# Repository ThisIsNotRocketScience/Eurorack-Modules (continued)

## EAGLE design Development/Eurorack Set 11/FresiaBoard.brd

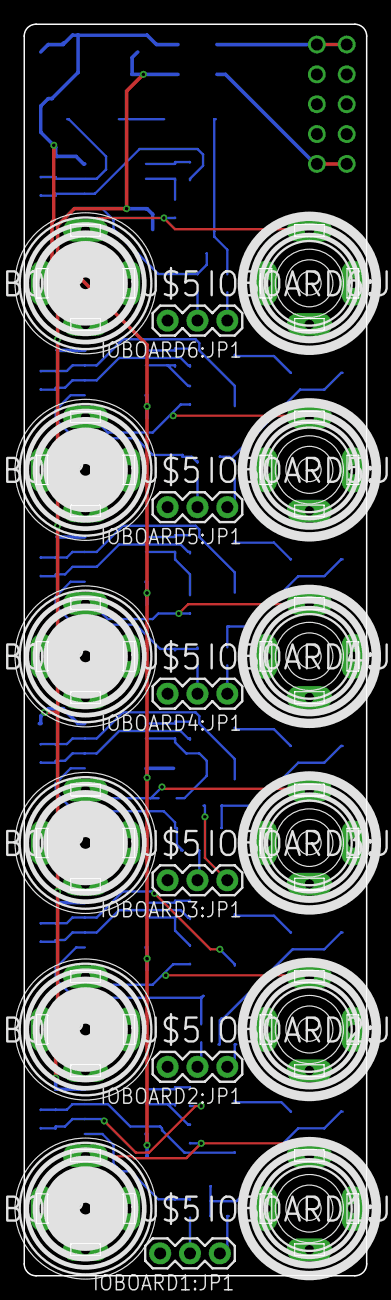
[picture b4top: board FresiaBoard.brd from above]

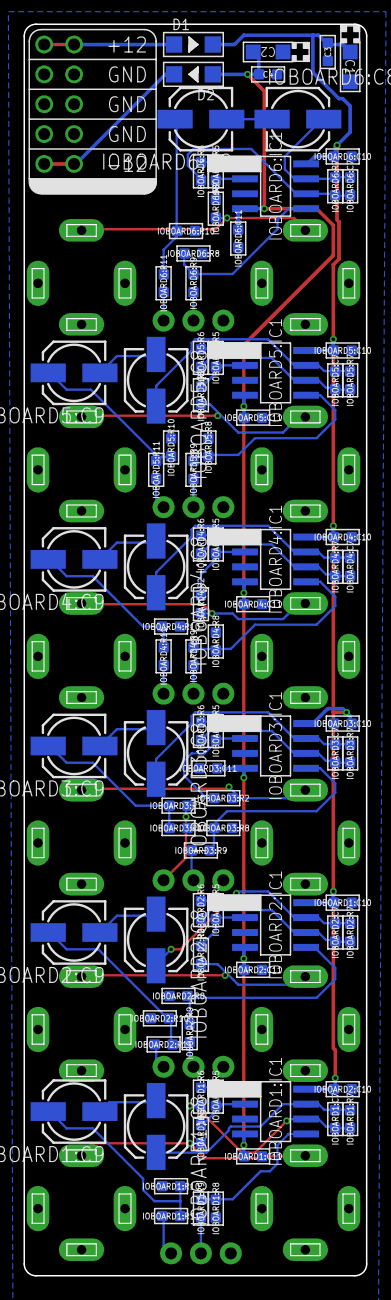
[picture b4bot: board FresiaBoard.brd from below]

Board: 2 copper layers, 29.1 x 106.5 mm, 110 parts (91 on the bottom side), 65 nets.

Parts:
C1, C2: 10uF; CASE-A_3216
C3, C4: 100nF; C0603
D1, D2: 1N4001; SOD123
IOBOARD1:C7, IOBOARD2:C7, IOBOARD3:C7, IOBOARD4:C7, IOBOARD5:C7, IOBOARD6:C7: 22p; C0603
IOBOARD1:C8, IOBOARD1:C9, IOBOARD2:C8, IOBOARD2:C9, IOBOARD3:C8, IOBOARD3:C9, IOBOARD4:C8, IOBOARD4:C9, IOBOARD5:C8, IOBOARD5:C9, IOBOARD6:C8, IOBOARD6:C9: 220uF; 153CLV-0505
IOBOARD1:C10, IOBOARD1:C11, IOBOARD2:C10, IOBOARD2:C11, IOBOARD3:C10, IOBOARD3:C11, IOBOARD4:C10, IOBOARD4:C11, IOBOARD5:C10, IOBOARD5:C11, IOBOARD6:C10, IOBOARD6:C11: 100nF; C0603
IOBOARD1:IC1, IOBOARD2:IC1, IOBOARD3:IC1, IOBOARD4:IC1, IOBOARD5:IC1, IOBOARD6:IC1: NE5532D; SO08
IOBOARD1:J1, IOBOARD2:J1, IOBOARD3:J1, IOBOARD4:J1, IOBOARD5:J1, IOBOARD6:J1: PJ-341; 3.5MM-JACK-SWITCH-13MM-OUTPUT
IOBOARD1:JP1, IOBOARD2:JP1, IOBOARD3:JP1, IOBOARD4:JP1, IOBOARD5:JP1, IOBOARD6:JP1: 1X03
IOBOARD1:R2, IOBOARD2:R2, IOBOARD3:R2, IOBOARD4:R2, IOBOARD5:R2, IOBOARD6:R2: 100k; R0603
IOBOARD1:R5, IOBOARD2:R5, IOBOARD3:R5, IOBOARD4:R5, IOBOARD5:R5, IOBOARD6:R5: 220k; R0603
IOBOARD1:R6, IOBOARD1:R7, IOBOARD2:R6, IOBOARD2:R7, IOBOARD3:R6, IOBOARD3:R7, IOBOARD4:R6, IOBOARD4:R7, IOBOARD5:R6, IOBOARD5:R7, IOBOARD6:R6, IOBOARD6:R7: 4.7k; R0603
IOBOARD1:R8, IOBOARD1:R9, IOBOARD2:R8, IOBOARD2:R9, IOBOARD3:R8, IOBOARD3:R9, IOBOARD4:R8, IOBOARD4:R9, IOBOARD5:R8, IOBOARD5:R9, IOBOARD6:R8, IOBOARD6:R9: 27; R0603
IOBOARD1:R10, IOBOARD2:R10, IOBOARD3:R10, IOBOARD4:R10, IOBOARD5:R10, IOBOARD6:R10: 22k; R0603
IOBOARD1:R11, IOBOARD2:R11, IOBOARD3:R11, IOBOARD4:R11, IOBOARD5:R11, IOBOARD6:R11: 56; R0603
IOBOARD1:U$5, IOBOARD2:U$5, IOBOARD3:U$5, IOBOARD4:U$5, IOBOARD5:U$5, IOBOARD6:U$5: PJ-341; 3.5MM-JACK-SWITCH-13MM-INPUT
PCB1: EURORACK_PCB6HP; EURORACK6HPPCB
U$1: POWER_SIMPLE10; POWER_10

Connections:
12V: C1.+, C3.2, D1.-, IOBOARD1:C10.1, IOBOARD1:IC1.8, IOBOARD2:C10.1, IOBOARD2:IC1.8, IOBOARD3:C10.1, IOBOARD3:IC1.8, IOBOARD4:C10.1, IOBOARD4:IC1.8, IOBOARD5:C10.1, IOBOARD5:IC1.8, IOBOARD6:C10.1, IOBOARD6:IC1.8
-12V: C2.-, C4.1, D2.+, IOBOARD1:C11.1, IOBOARD1:IC1.4, IOBOARD2:C11.1, IOBOARD2:IC1.4, IOBOARD3:C11.1, IOBOARD3:IC1.4, IOBOARD4:C11.1, IOBOARD4:IC1.4, IOBOARD5:C11.1, IOBOARD5:IC1.4, IOBOARD6:C11.1, IOBOARD6:IC1.4
GND: C1.-, C2.+, C3.1, C4.2, IOBOARD1:C10.2, IOBOARD1:C11.2, IOBOARD1:IC1.3, IOBOARD1:J1.RING@3, IOBOARD1:JP1.3, IOBOARD1:R8.2, IOBOARD1:R10.1, IOBOARD1:U$5.RING@3, IOBOARD1:U$5.SWITCH@3, IOBOARD2:C10.2, IOBOARD2:C11.2, IOBOARD2:IC1.3, IOBOARD2:J1.RING@3, IOBOARD2:JP1.3, IOBOARD2:R8.2, IOBOARD2:R10.1, IOBOARD2:U$5.RING@3, IOBOARD2:U$5.SWITCH@3, IOBOARD3:C10.2, IOBOARD3:C11.2, IOBOARD3:IC1.3, IOBOARD3:J1.RING@3, IOBOARD3:JP1.3, IOBOARD3:R8.2, IOBOARD3:R10.1, IOBOARD3:U$5.RING@3, IOBOARD3:U$5.SWITCH@3, IOBOARD4:C10.2, IOBOARD4:C11.2, IOBOARD4:IC1.3, IOBOARD4:J1.RING@3, IOBOARD4:JP1.3, IOBOARD4:R8.2, IOBOARD4:R10.1, IOBOARD4:U$5.RING@3, IOBOARD4:U$5.SWITCH@3, IOBOARD5:C10.2, IOBOARD5:C11.2, IOBOARD5:IC1.3, IOBOARD5:J1.RING@3, IOBOARD5:JP1.3, IOBOARD5:R8.2, IOBOARD5:R10.1, IOBOARD5:U$5.RING@3, IOBOARD5:U$5.SWITCH@3, IOBOARD6:C10.2, IOBOARD6:C11.2, IOBOARD6:IC1.3, IOBOARD6:J1.RING@3, IOBOARD6:JP1.3, IOBOARD6:R8.2, IOBOARD6:R10.1, IOBOARD6:U$5.RING@3, IOBOARD6:U$5.SWITCH@3, U$1.3, U$1.4, U$1.5, U$1.6, U$1.7, U$1.8
IOBOARD1:N$2: IOBOARD1:C7.1, IOBOARD1:C8.+, IOBOARD1:IC1.7, IOBOARD1:R7.1
IOBOARD1:N$3: IOBOARD1:IC1.5, IOBOARD1:R8.1, IOBOARD1:R9.1
IOBOARD1:N$4: IOBOARD1:C7.2, IOBOARD1:IC1.6, IOBOARD1:R6.1, IOBOARD1:R7.2
IOBOARD1:N$5: IOBOARD1:IC1.2, IOBOARD1:R2.2, IOBOARD1:R5.2
IOBOARD1:N$6: IOBOARD1:IC1.1, IOBOARD1:R5.1, IOBOARD1:R6.2
IOBOARD1:N$7: IOBOARD1:J1.TIP@3, IOBOARD1:R2.1, IOBOARD1:U$5.TIP@3
IOBOARD1:N$8: IOBOARD1:C8.-, IOBOARD1:C9.-
IOBOARD1:N$9: IOBOARD1:C9.+, IOBOARD1:R10.2, IOBOARD1:R11.2
IOBOARD1:RIGHT_MID: IOBOARD1:JP1.2, IOBOARD1:R9.2
IOBOARD1:RIGHT_TIP: IOBOARD1:JP1.1, IOBOARD1:R11.1
IOBOARD2:N$2: IOBOARD2:C7.1, IOBOARD2:C8.+, IOBOARD2:IC1.7, IOBOARD2:R7.1
IOBOARD2:N$3: IOBOARD2:IC1.5, IOBOARD2:R8.1, IOBOARD2:R9.1
IOBOARD2:N$4: IOBOARD2:C7.2, IOBOARD2:IC1.6, IOBOARD2:R6.1, IOBOARD2:R7.2
IOBOARD2:N$5: IOBOARD2:IC1.2, IOBOARD2:R2.2, IOBOARD2:R5.2
IOBOARD2:N$6: IOBOARD2:IC1.1, IOBOARD2:R5.1, IOBOARD2:R6.2
IOBOARD2:N$7: IOBOARD2:J1.TIP@3, IOBOARD2:R2.1, IOBOARD2:U$5.TIP@3
IOBOARD2:N$8: IOBOARD2:C8.-, IOBOARD2:C9.-
IOBOARD2:N$9: IOBOARD2:C9.+, IOBOARD2:R10.2, IOBOARD2:R11.2
IOBOARD2:RIGHT_MID: IOBOARD2:JP1.2, IOBOARD2:R9.2
IOBOARD2:RIGHT_TIP: IOBOARD2:JP1.1, IOBOARD2:R11.1
IOBOARD3:N$2: IOBOARD3:C7.1, IOBOARD3:C8.+, IOBOARD3:IC1.7, IOBOARD3:R7.1
IOBOARD3:N$3: IOBOARD3:IC1.5, IOBOARD3:R8.1, IOBOARD3:R9.1
IOBOARD3:N$4: IOBOARD3:C7.2, IOBOARD3:IC1.6, IOBOARD3:R6.1, IOBOARD3:R7.2
IOBOARD3:N$5: IOBOARD3:IC1.2, IOBOARD3:R2.2, IOBOARD3:R5.2
IOBOARD3:N$6: IOBOARD3:IC1.1, IOBOARD3:R5.1, IOBOARD3:R6.2
IOBOARD3:N$7: IOBOARD3:J1.TIP@3, IOBOARD3:R2.1, IOBOARD3:U$5.TIP@3
IOBOARD3:N$8: IOBOARD3:C8.-, IOBOARD3:C9.-
IOBOARD3:N$9: IOBOARD3:C9.+, IOBOARD3:R10.2, IOBOARD3:R11.2
IOBOARD3:RIGHT_MID: IOBOARD3:JP1.2, IOBOARD3:R9.2
IOBOARD3:RIGHT_TIP: IOBOARD3:JP1.1, IOBOARD3:R11.1
IOBOARD4:N$2: IOBOARD4:C7.1, IOBOARD4:C8.+, IOBOARD4:IC1.7, IOBOARD4:R7.1
IOBOARD4:N$3: IOBOARD4:IC1.5, IOBOARD4:R8.1, IOBOARD4:R9.1
IOBOARD4:N$4: IOBOARD4:C7.2, IOBOARD4:IC1.6, IOBOARD4:R6.1, IOBOARD4:R7.2
IOBOARD4:N$5: IOBOARD4:IC1.2, IOBOARD4:R2.2, IOBOARD4:R5.2
IOBOARD4:N$6: IOBOARD4:IC1.1, IOBOARD4:R5.1, IOBOARD4:R6.2
IOBOARD4:N$7: IOBOARD4:J1.TIP@3, IOBOARD4:R2.1, IOBOARD4:U$5.TIP@3
IOBOARD4:N$8: IOBOARD4:C8.-, IOBOARD4:C9.-
IOBOARD4:N$9: IOBOARD4:C9.+, IOBOARD4:R10.2, IOBOARD4:R11.2
IOBOARD4:RIGHT_MID: IOBOARD4:JP1.2, IOBOARD4:R9.2
IOBOARD4:RIGHT_TIP: IOBOARD4:JP1.1, IOBOARD4:R11.1
IOBOARD5:N$2: IOBOARD5:C7.1, IOBOARD5:C8.+, IOBOARD5:IC1.7, IOBOARD5:R7.1
IOBOARD5:N$3: IOBOARD5:IC1.5, IOBOARD5:R8.1, IOBOARD5:R9.1
IOBOARD5:N$4: IOBOARD5:C7.2, IOBOARD5:IC1.6, IOBOARD5:R6.1, IOBOARD5:R7.2
IOBOARD5:N$5: IOBOARD5:IC1.2, IOBOARD5:R2.2, IOBOARD5:R5.2
IOBOARD5:N$6: IOBOARD5:IC1.1, IOBOARD5:R5.1, IOBOARD5:R6.2
IOBOARD5:N$7: IOBOARD5:J1.TIP@3, IOBOARD5:R2.1, IOBOARD5:U$5.TIP@3
IOBOARD5:N$8: IOBOARD5:C8.-, IOBOARD5:C9.-
IOBOARD5:N$9: IOBOARD5:C9.+, IOBOARD5:R10.2, IOBOARD5:R11.2
IOBOARD5:RIGHT_MID: IOBOARD5:JP1.2, IOBOARD5:R9.2
IOBOARD5:RIGHT_TIP: IOBOARD5:JP1.1, IOBOARD5:R11.1
IOBOARD6:N$2: IOBOARD6:C7.1, IOBOARD6:C8.+, IOBOARD6:IC1.7, IOBOARD6:R7.1
IOBOARD6:N$3: IOBOARD6:IC1.5, IOBOARD6:R8.1, IOBOARD6:R9.1
IOBOARD6:N$4: IOBOARD6:C7.2, IOBOARD6:IC1.6, IOBOARD6:R6.1, IOBOARD6:R7.2
IOBOARD6:N$5: IOBOARD6:IC1.2, IOBOARD6:R2.2, IOBOARD6:R5.2
IOBOARD6:N$6: IOBOARD6:IC1.1, IOBOARD6:R5.1, IOBOARD6:R6.2
IOBOARD6:N$7: IOBOARD6:J1.TIP@3, IOBOARD6:R2.1, IOBOARD6:U$5.TIP@3
IOBOARD6:N$8: IOBOARD6:C8.-, IOBOARD6:C9.-
IOBOARD6:N$9: IOBOARD6:C9.+, IOBOARD6:R10.2, IOBOARD6:R11.2
IOBOARD6:RIGHT_MID: IOBOARD6:JP1.2, IOBOARD6:R9.2
IOBOARD6:RIGHT_TIP: IOBOARD6:JP1.1, IOBOARD6:R11.1
unnamed: D2.-, U$1.1, U$1.2
unnamed: D1.+, U$1.9, U$1.10

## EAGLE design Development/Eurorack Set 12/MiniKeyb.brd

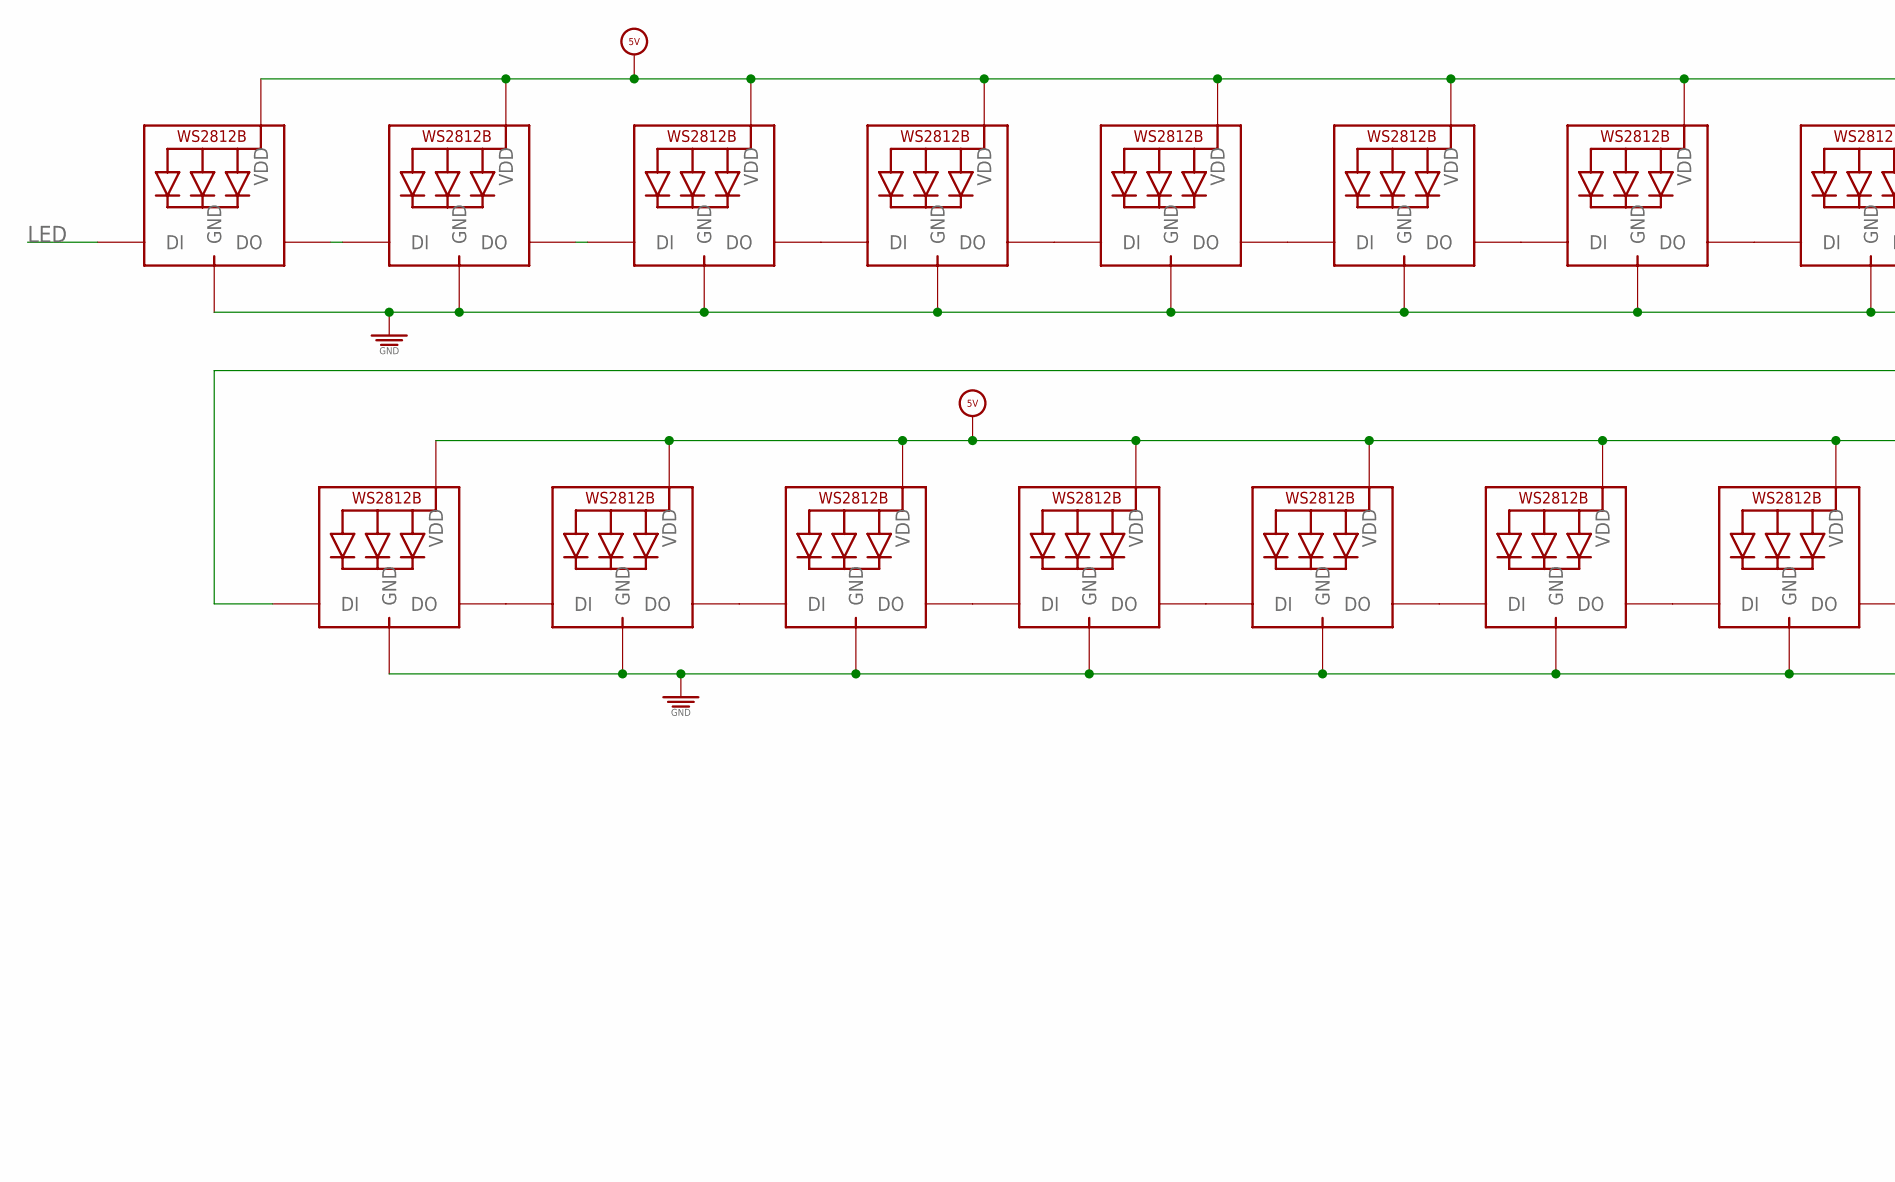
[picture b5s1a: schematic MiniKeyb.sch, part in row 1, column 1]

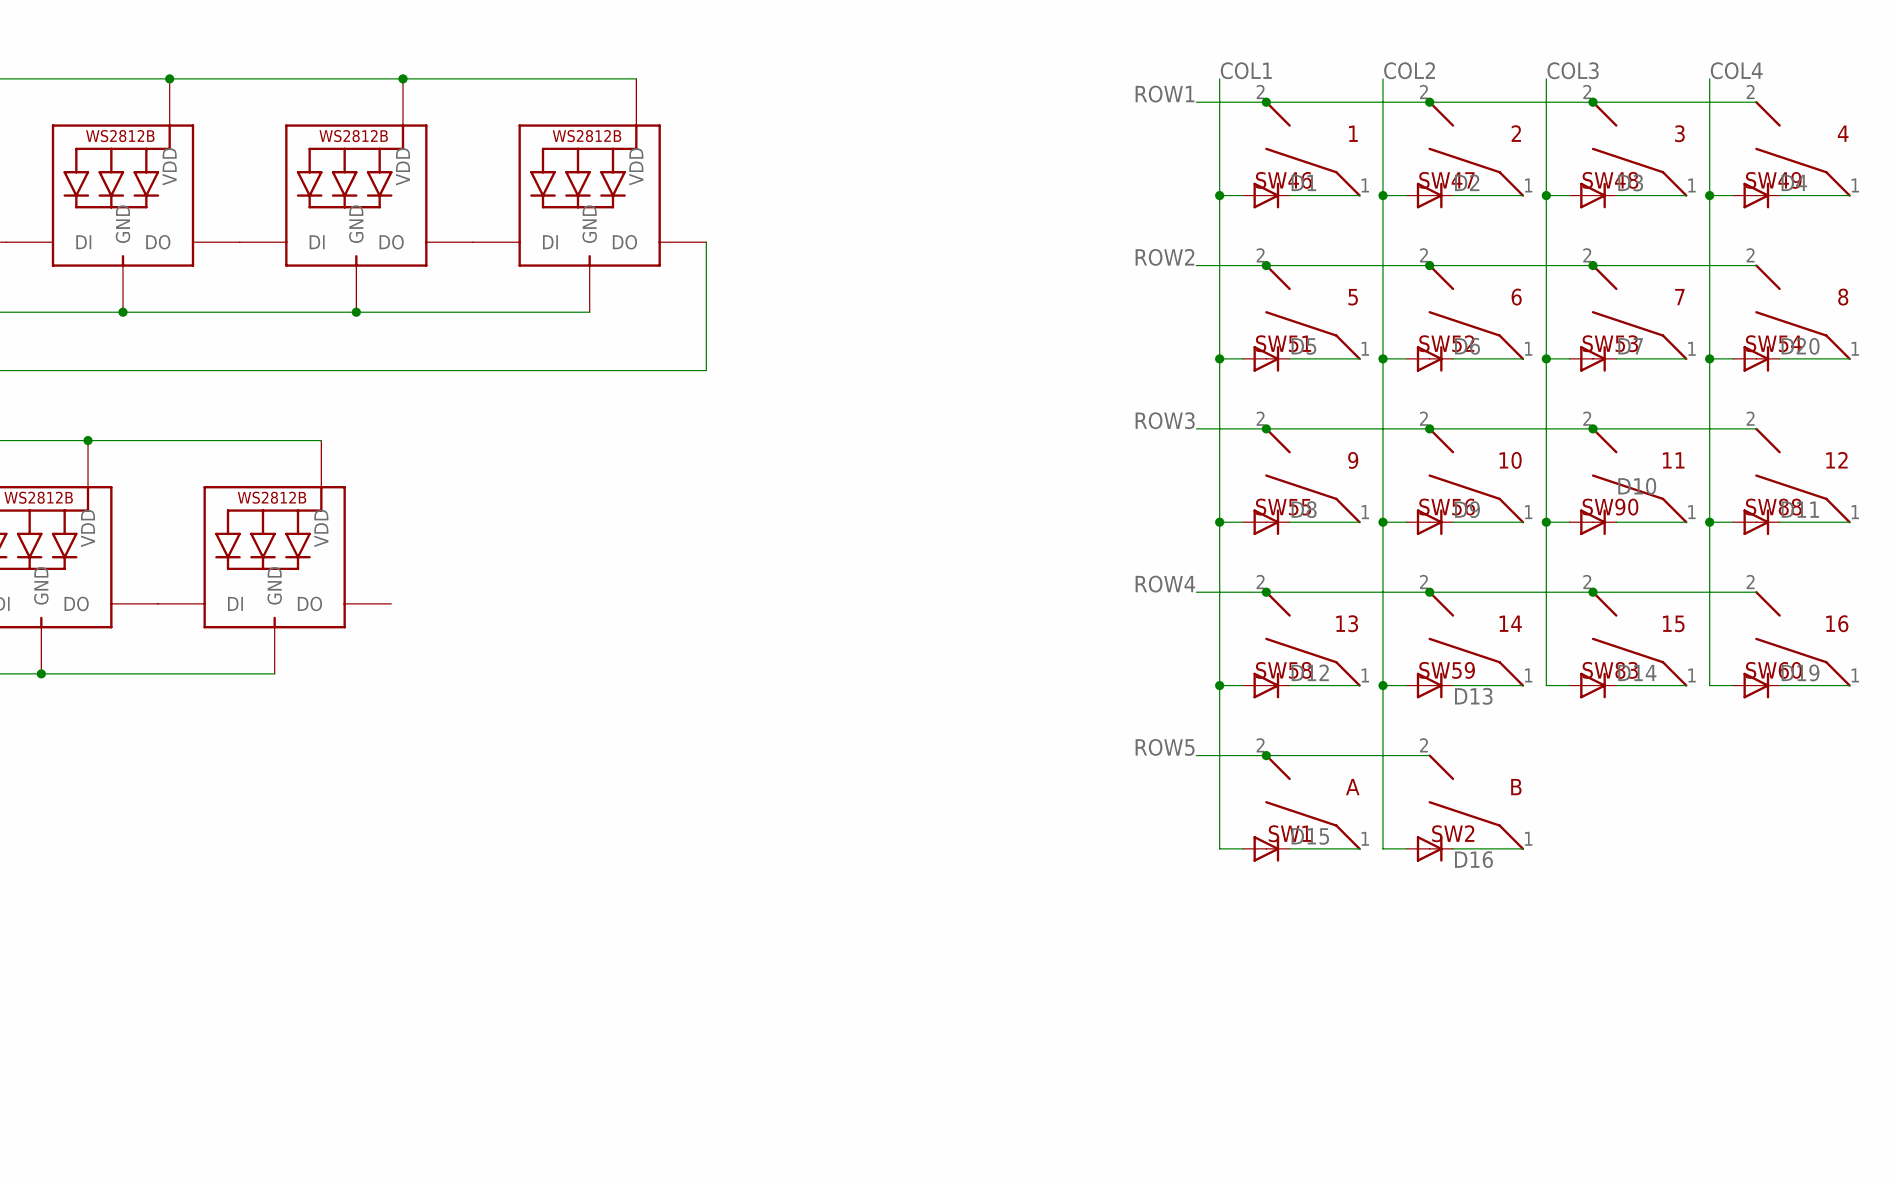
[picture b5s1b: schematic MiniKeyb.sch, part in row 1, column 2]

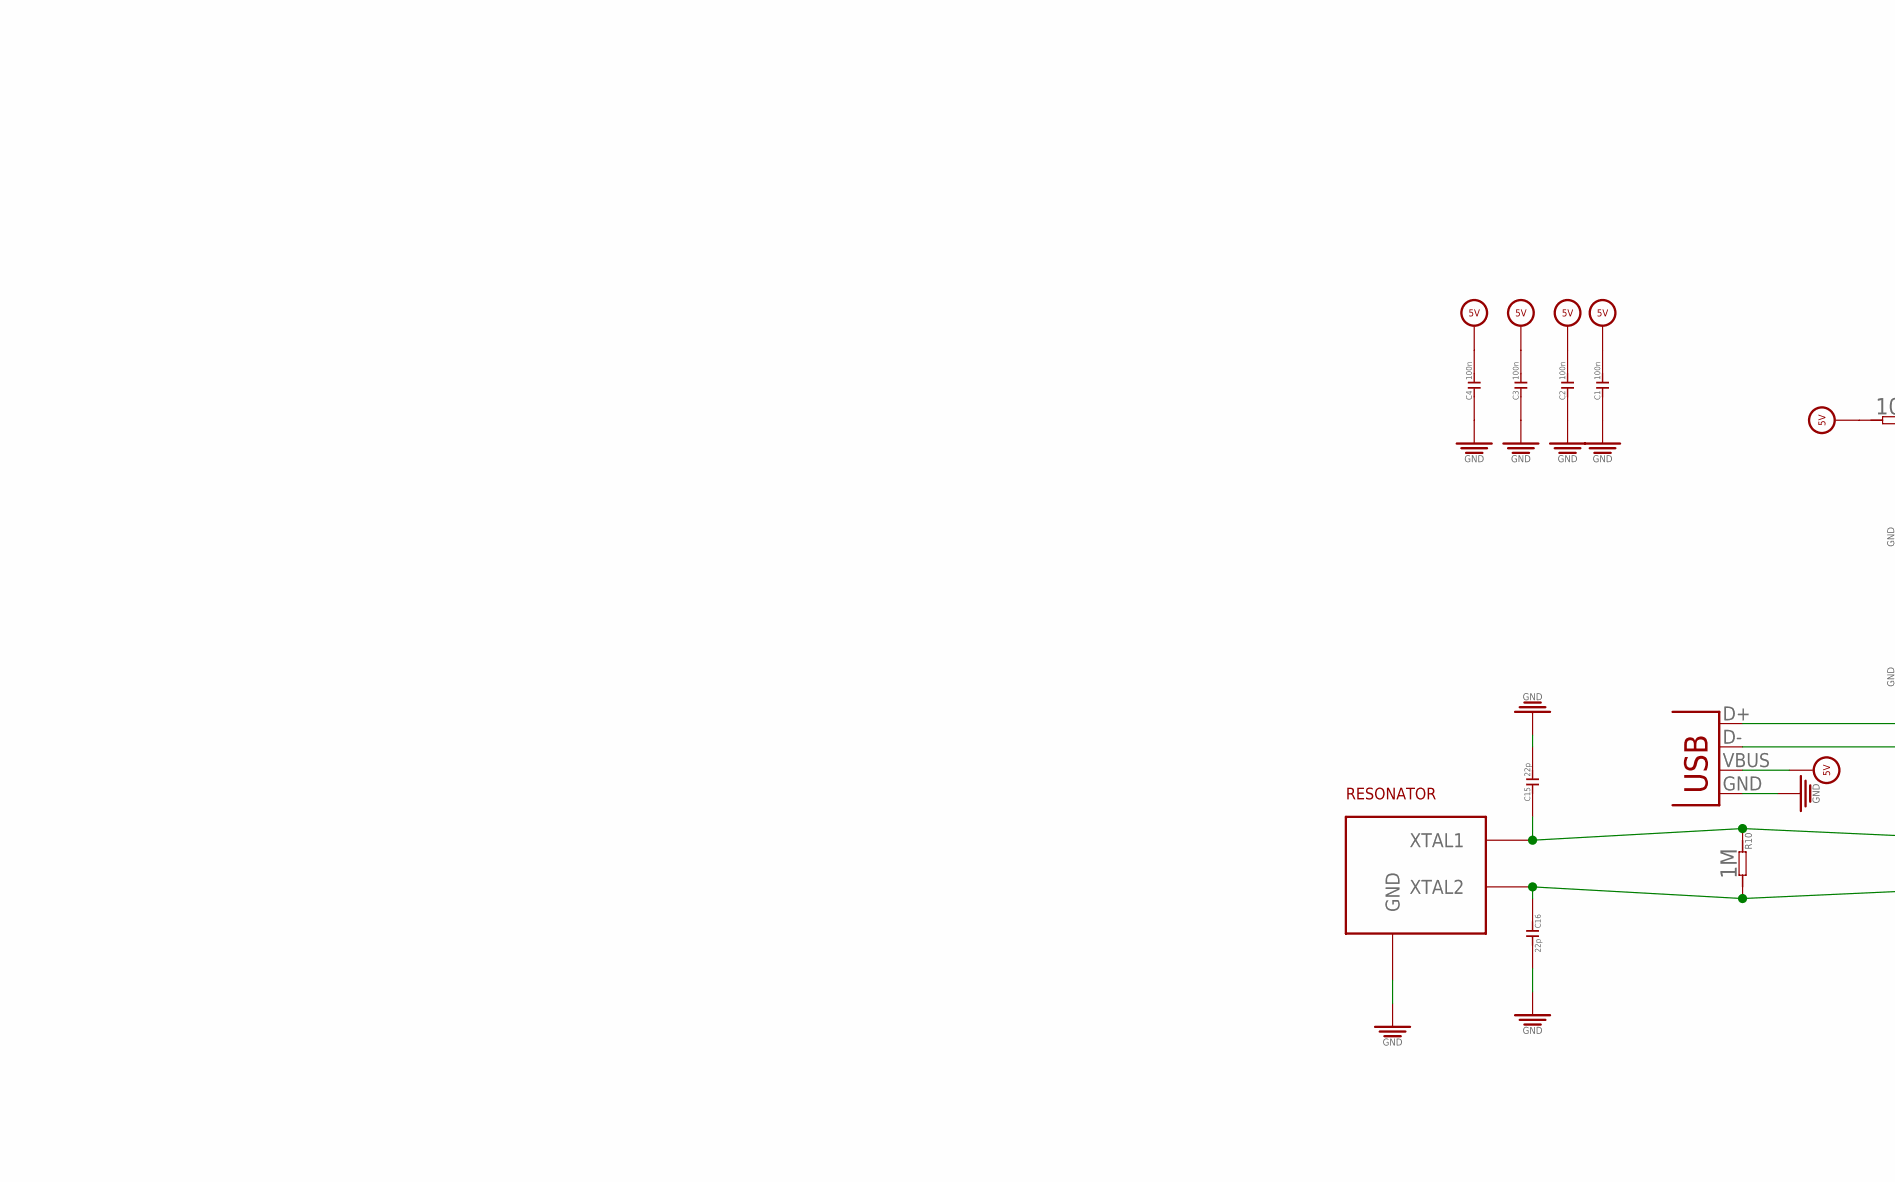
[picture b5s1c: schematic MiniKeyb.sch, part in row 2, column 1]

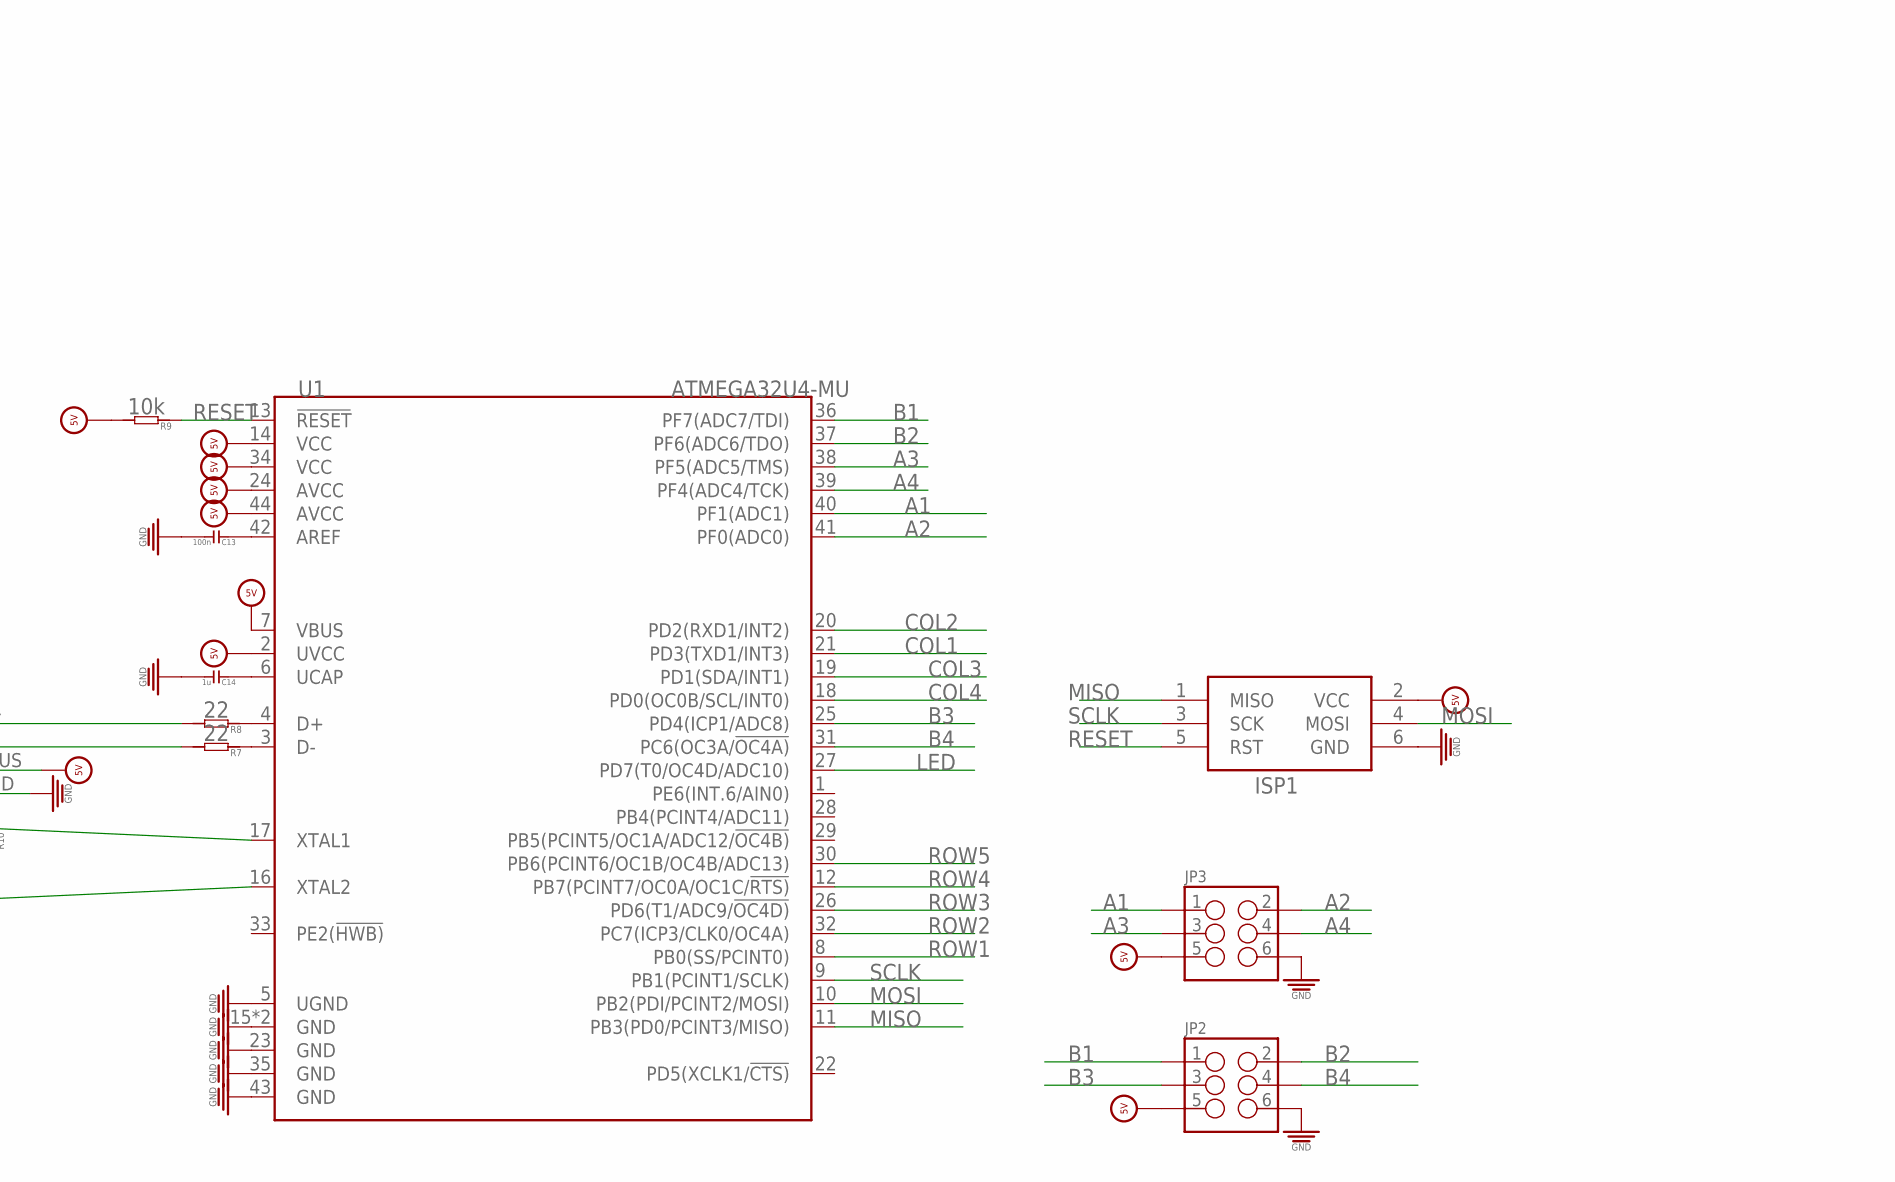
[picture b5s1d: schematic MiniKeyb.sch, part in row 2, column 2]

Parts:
C1, C2, C3, C4, C13: 100n; C0603
C14: 1u; C0603
C15, C16: 22p; C0603
D1, D2, D3, D4, D5, D6, D7, D8, D9, D10, D11, D12, D13, D14, D15, D16, D19, D20: CGRM4001-G; SOD-123_MINI-SMA
ISP1: AVRISP-6; AVRISP
JP1: USB-B; USB-B-PTH
JP2, JP3: M03X2; 2X3-SHROUDED
LED1, LED2, LED13, LED14, LED15, LED16, LED17, LED18, LED19, LED20, LED21, LED22, LED23, LED24, LED25, LED26, LED27, LED28: WS2812B3535; LED3535
R7, R8: 22; R0603
R9: 10k; R0603
R10: 1M; R0603
SW1: A; MX1A-XXNW
SW2: B; MX1A-XXNW
SW46: 1; MX1A-XXNW
SW47: 2; MX1A-XXNW
SW48: 3; MX1A-XXNW
SW49: 4; MX1A-XXNW
SW51: 5; MX1A-XXNW
SW52: 6; MX1A-XXNW
SW53: 7; MX1A-XXNW
SW54: 8; MX1A-XXNW
SW55: 9; MX1A-XXNW
SW56: 10; MX1A-XXNW
SW58: 13; MX1A-XXNW
SW59: 14; MX1A-XXNW
SW60: 16; MX1A-XXNW
SW83: 15; MX1A-XXNW
SW88: 12; MX1A-XXNW
SW90: 11; MX1A-XXNW
U1: ATMEGA32U4-MU; QFN44
U$60: RESONATOR; 16MHZXTAL

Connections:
5V: C1.2, C2.2, C3.2, C4.2, ISP1.2 (VCC), JP1.VBUS, JP2.5, JP3.5, LED1.1 (VDD), LED2.1 (VDD), LED13.1 (VDD), LED14.1 (VDD), LED15.1 (VDD), LED16.1 (VDD), LED17.1 (VDD), LED18.1 (VDD), LED19.1 (VDD), LED20.1 (VDD), LED21.1 (VDD), LED22.1 (VDD), LED23.1 (VDD), LED24.1 (VDD), LED25.1 (VDD), LED26.1 (VDD), LED27.1 (VDD), LED28.1 (VDD), R9.2, U1.2 (UVCC), U1.7 (VBUS), U1.14 (VCC), U1.24 (AVCC), U1.34 (VCC), U1.44 (AVCC)
A1: JP3.1, U1.40 (PF1(ADC1))
A2: JP3.2, U1.41 (PF0(ADC0))
A3: JP3.3, U1.38 (PF5(ADC5/TMS))
A4: JP3.4, U1.39 (PF4(ADC4/TCK))
B1: JP2.1, U1.36 (PF7(ADC7/TDI))
B2: JP2.2, U1.37 (PF6(ADC6/TDO))
B3: JP2.3, U1.25 (PD4(ICP1/ADC8))
B4: JP2.4, U1.31 (PC6(OC3A/!OC4A))
COL1: D1.A, D5.A, D8.A, D12.A, D15.A, U1.21 (PD3(TXD1/INT3))
COL2: D2.A, D6.A, D9.A, D13.A, D16.A, U1.20 (PD2(RXD1/INT2))
COL3: D3.A, D7.A, D10.A, D14.A, U1.19 (PD1(SDA/INT1))
COL4: D4.A, D11.A, D19.A, D20.A, U1.18 (PD0(OC0B/SCL/INT0))
GND: C1.1, C2.1, C3.1, C4.1, C13.2, C14.2, C15.2, C16.2, ISP1.6 (GND), JP1.GND, JP2.6, JP3.6, LED1.3 (GND), LED2.3 (GND), LED13.3 (GND), LED14.3 (GND), LED15.3 (GND), LED16.3 (GND), LED17.3 (GND), LED18.3 (GND), LED19.3 (GND), LED20.3 (GND), LED21.3 (GND), LED22.3 (GND), LED23.3 (GND), LED24.3 (GND), LED25.3 (GND), LED26.3 (GND), LED27.3 (GND), LED28.3 (GND), U1.5 (UGND), U1.15 (GND), U1.23 (GND), U1.35 (GND), U1.43 (GND), U1.TAB (GND), U$60.P$2 (GND), U$60.P$4 (GND)
LED: LED13.4 (DI), U1.27 (PD7(T0/OC4D/ADC10))
MISO: ISP1.1 (MISO), U1.11 (PB3(PD0/PCINT3/MISO))
MOSI: ISP1.4 (MOSI), U1.10 (PB2(PDI/PCINT2/MOSI))
unnamed: D1.C, SW46.1
unnamed: D2.C, SW47.1
unnamed: D3.C, SW48.1
unnamed: D4.C, SW49.1
unnamed: D5.C, SW51.1
unnamed: D6.C, SW52.1
unnamed: D7.C, SW53.1
unnamed: D8.C, SW55.1
unnamed: D9.C, SW56.1
unnamed: D10.C, SW90.1
unnamed: D11.C, SW88.1
unnamed: D12.C, SW58.1
unnamed: D13.C, SW59.1
unnamed: D14.C, SW83.1
unnamed: D15.C, SW1.1
unnamed: D16.C, SW2.1
unnamed: LED1.2 (DO), LED2.4 (DI)
unnamed: LED1.4 (DI), LED28.2 (DO)
unnamed: D19.C, SW60.1
unnamed: D20.C, SW54.1
unnamed: LED13.2 (DO), LED14.4 (DI)
unnamed: LED14.2 (DO), LED15.4 (DI)
unnamed: LED15.2 (DO), LED16.4 (DI)
unnamed: LED16.2 (DO), LED17.4 (DI)
unnamed: LED18.2 (DO), LED19.4 (DI)
unnamed: LED19.2 (DO), LED20.4 (DI)
unnamed: LED20.2 (DO), LED21.4 (DI)
unnamed: LED21.2 (DO), LED22.4 (DI)
unnamed: LED17.2 (DO), LED18.4 (DI)
unnamed: LED27.2 (DO), LED28.4 (DI)
unnamed: LED23.2 (DO), LED24.4 (DI)
unnamed: LED24.2 (DO), LED25.4 (DI)
unnamed: LED25.2 (DO), LED26.4 (DI)
unnamed: LED26.2 (DO), LED27.4 (DI)
unnamed: LED22.2 (DO), LED23.4 (DI)
unnamed: JP1.D-, R7.2
unnamed: JP1.D+, R8.2
unnamed: C13.1, U1.42 (AREF)
unnamed: R8.1, U1.4 (D+)
unnamed: R7.1, U1.3 (D-)
unnamed: C14.1, U1.6 (UCAP)
unnamed: C15.1, R10.1, U1.17 (XTAL1), U$60.P$1 (XTAL1)
unnamed: C16.1, R10.2, U1.16 (XTAL2), U$60.P$3 (XTAL2)
RESET: ISP1.5 (RST), R9.1, U1.13 (!RESET)
ROW1: SW46.2, SW47.2, SW48.2, SW49.2, U1.8 (PB0(SS/PCINT0))
ROW2: SW51.2, SW52.2, SW53.2, SW54.2, U1.32 (PC7(ICP3/CLK0/OC4A))
ROW3: SW55.2, SW56.2, SW88.2, SW90.2, U1.26 (PD6(T1/ADC9/!OC4D))
ROW4: SW58.2, SW59.2, SW60.2, SW83.2, U1.12 (PB7(PCINT7/OC0A/OC1C/!RTS))
ROW5: SW1.2, SW2.2, U1.30 (PB6(PCINT6/OC1B/OC4B/ADC13))
SCLK: ISP1.3 (SCK), U1.9 (PB1(PCINT1/SCLK))

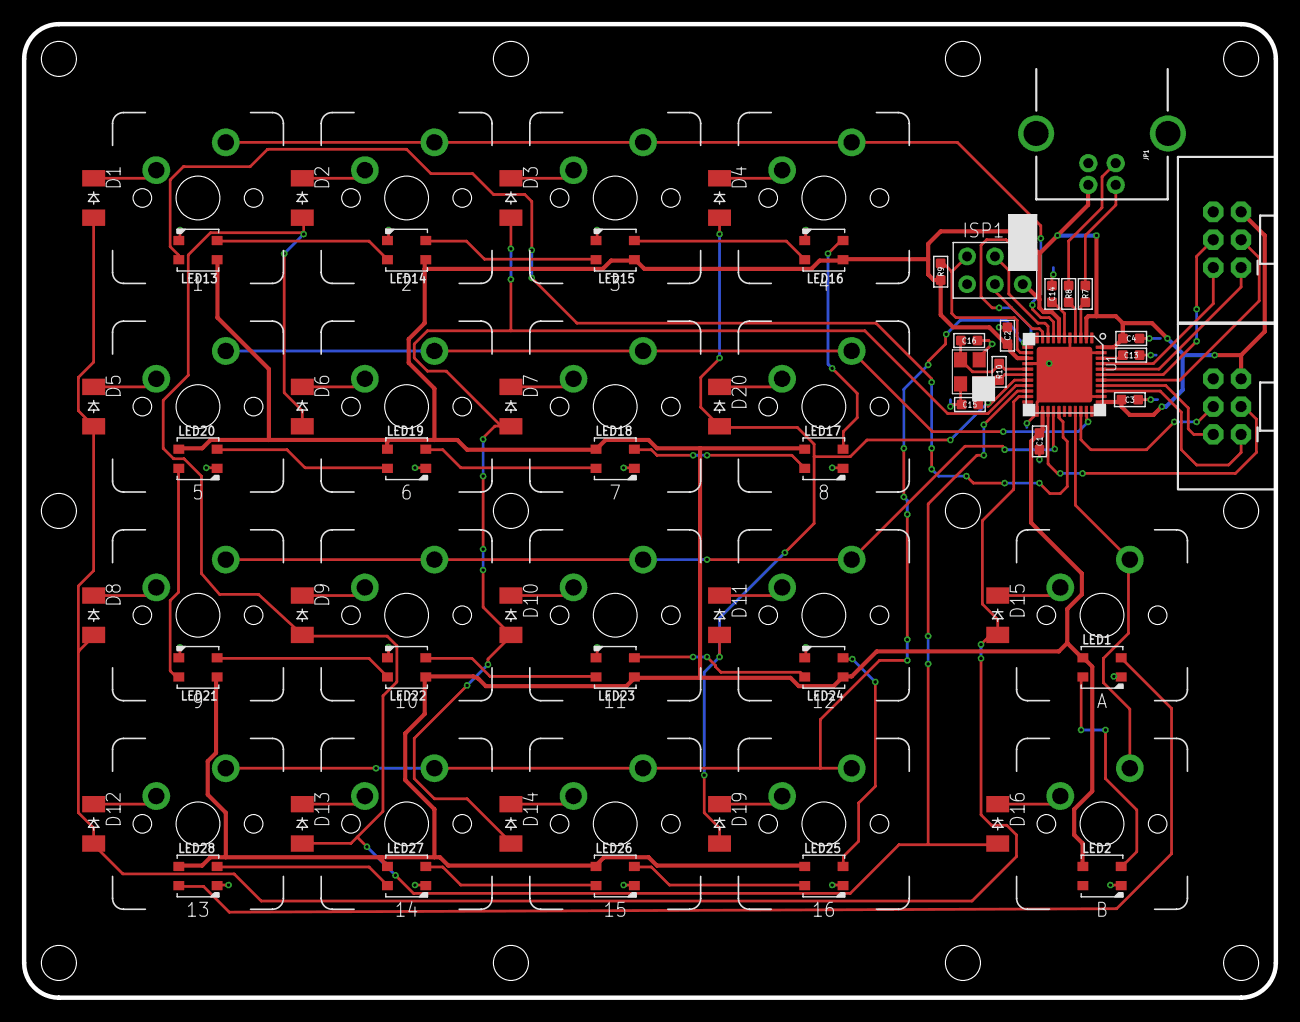
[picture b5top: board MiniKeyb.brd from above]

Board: 2 copper layers, 114.3 x 88.9 mm, 72 parts (0 on the bottom side), 67 nets.

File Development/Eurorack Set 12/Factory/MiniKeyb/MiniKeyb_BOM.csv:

Comment,Designator,Footprint,LCSC Part #
CGRM4001-G,"D1, D10, D11, D12, D13, D14, D19, D2, D20, D3, D4, D5, D6, D7, D8, D9, D15, D16",SOD-123_MINI-SMA,
1,"SW46",MX1A-XXNW,
2,"SW47",MX1A-XXNW,
3,"SW48",MX1A-XXNW,
4,"SW49",MX1A-XXNW,
5,"SW51",MX1A-XXNW,
6,"SW52",MX1A-XXNW,
7,"SW53",MX1A-XXNW,
8,"SW54",MX1A-XXNW,
9,"SW55",MX1A-XXNW,
10,"SW56",MX1A-XXNW,
13,"SW58",MX1A-XXNW,
14,"SW59",MX1A-XXNW,
16,"SW60",MX1A-XXNW,
15,"SW83",MX1A-XXNW,
12,"SW88",MX1A-XXNW,
11,"SW90",MX1A-XXNW,
A,"SW1",MX1A-XXNW,
B,"SW2",MX1A-XXNW,
WS2812B3535,"LED13, LED14, LED15, LED16, LED17, LED18, LED19, LED20, LED21, LED22, LED23, LED24, LED25, LED26, LED27, LED28, LED1, LED2",LED3535,
ATMEGA32U4-MU,"U1",QFN44,
USB-B,"JP1",USB-B-PTH,
22,"R7, R8",R0603,
10k,"R9",R0603,
1M,"R10",R0603,
100n,"C13, C1, C2, C3, C4",C0603,
1u,"C14",C0603,
22p,"C15, C16",C0603,
AVRISP-6,"ISP1",AVRISP,
RESONATOR,"U$60",16MHZXTAL,
,"JP2, JP3",2X3-SHROUDED,
